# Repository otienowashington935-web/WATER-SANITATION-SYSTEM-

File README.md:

# WATER-SANITATION-SYSTEM-
WATER DOZING AND SANITATITION

# COLLABORATORS
1. Masika Stephanie - Supervisor

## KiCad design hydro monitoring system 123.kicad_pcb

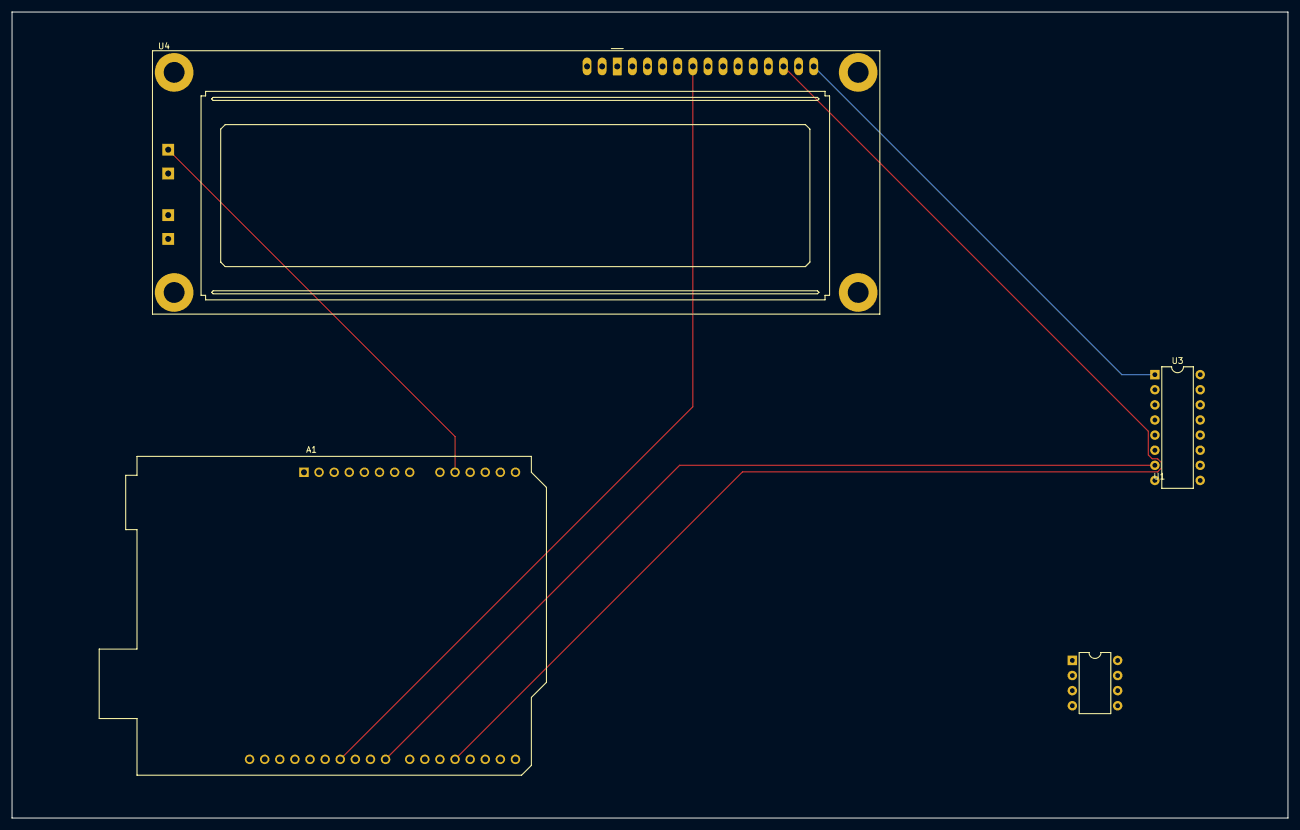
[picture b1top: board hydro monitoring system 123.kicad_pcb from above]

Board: 2 copper layers, 214.5 x 135.5 mm, 4 parts (0 on the bottom side), 11 nets.

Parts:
A1: Arduino_UNO_R3
U1: DS1307+; DIP-8_W7.62mm
U3: L293D; DIP-16_W7.62mm
U4: LCD-016N002L

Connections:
unnamed: A1.10 (A1), U4.A1
unnamed: A1.17 (D2), U3.1 (EN1,2), U4.14 (DB7)
unnamed: A1.18 (D3), U4.13 (DB6)
unnamed: A1.19 (D4), U4.12 (DB5)
unnamed: A1.20 (D5), U4.11 (DB4)
unnamed: A1.23 (D8), U3.7 (2A)
unnamed: A1.24 (D9), U3.2 (1A)
unnamed: A1.26 (D11), U4.6 (E)
unnamed: A1.27 (D12), U4.4 (RS)
unnamed: A1.14 (SCL/A5), U1.6 (SCL)
unnamed: A1.13 (SDA/A4), U1.5 (SDA)
